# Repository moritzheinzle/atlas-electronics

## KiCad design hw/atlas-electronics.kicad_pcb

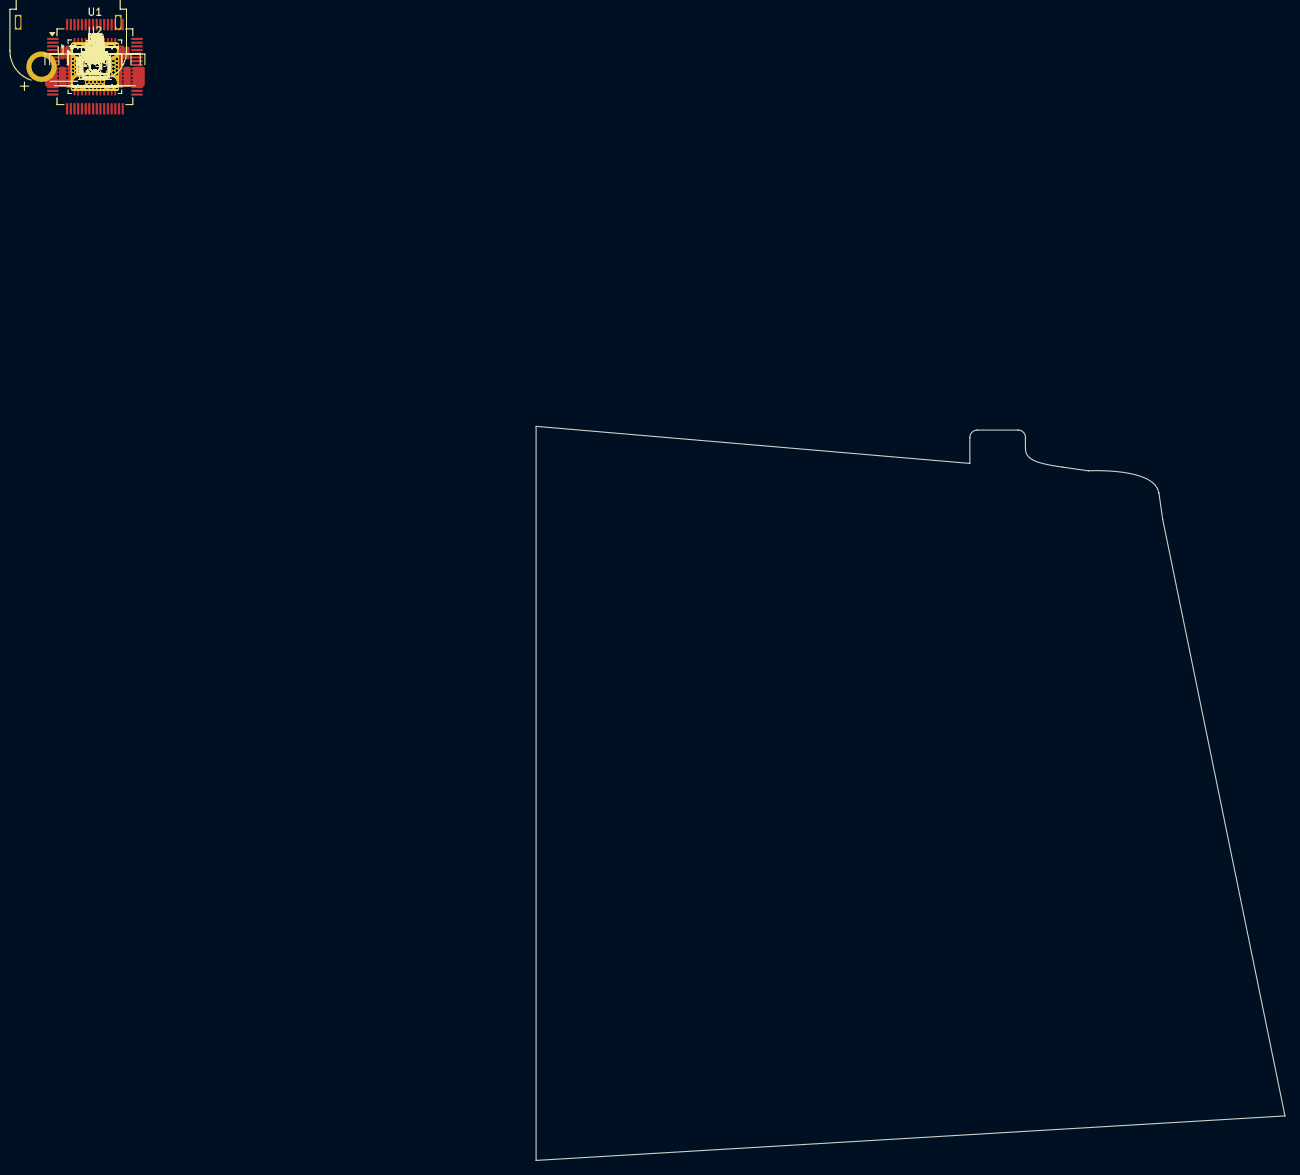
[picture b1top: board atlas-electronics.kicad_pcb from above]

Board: 2 copper layers, 101.0 x 99.0 mm, 185 parts (0 on the bottom side), 95 nets, no tracks yet.

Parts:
C1, C3, C4, C5, C6, C8, C11, C14, C17, C18, C24, C27, C30, C37, C38, C40, C41, C42, C43, C44, C45: 100n X7R 50V; C_0603_1608Metric
C2, C10, C39: 4u7 X5R 16V; C_0603_1608Metric
C7, C9, C12, C16: 1u X5R 50V; C_0603_1608Metric
C13, C19, C25, C26, C28, C29, C31, C32: 4u7 X7R 50V; C_1206_3216Metric
C15: 47n X7R 50V; C_0603_1608Metric
C20: 10u X5R 25V; C_0805_2012Metric
C21, C22, C23, C33, C34, C35: 3n3 X7R 100V; C_0603_1608Metric
C36: 10n X7R 50V; C_0603_1608Metric
C46, C47, C48, C49, C50, C51, C52, C53, C55, C56, C57, C58, C59, C60: C_Small; C_0603_1608Metric
C54, C61: 100n; WDFN-10-1EP_3x3mm_P0.5mm_EP1.8x2.5mm
C62: C_Small; WDFN-10-1EP_3x3mm_P0.5mm_EP1.8x2.5mm
C63, C64: 10pF; C_0603_1608Metric
C65, C66, C67, C68: 1u X7R 25V; C_0603_1608Metric
D1: SS16; D_SOD-123
D2, D3, D4: 1A 40V; D_SOD-123
D5, D6#2, D7#2, D8#2, D9: SK6805; LED_SK6812_EC15_1.5x1.5mm
D6, D7, D8, D9#2: SK6805; LED_SK6805_PLCC4_2.4x2.7mm_P1.3mm
D10: PESD2CANFD24V-TR; SOT-23
D11, D12: BAT48ZFILM; D_SOD-123
D13: SD05C-01F; D_SOD-323
D14, D15: GREEN; LED_0805_2012Metric
FB1: 120@100MHz; L_0603_1608Metric
J1, J2, J3: Conn_01x01; Goated holy pad
J4, J6, J10: Conn_01x03_MountingPin; JST_GH_SM03B-GHS-TB_1x03-1MP_P1.25mm_Horizontal
J5: Conn_01x08_MountingPin; JST_GH_SM08B-GHS-TB_1x08-1MP_P1.25mm_Horizontal
J7: Conn_01x05_MountingPin; JST_GH_SM05B-GHS-TB_1x05-1MP_P1.25mm_Horizontal
J8: Conn_01x07_MountingPin; JST_GH_SM07B-GHS-TB_1x07-1MP_P1.25mm_Horizontal
J9: Conn_01x06_MountingPin; AMASS_XT60PW-F_1x02_P7.20mm_Horizontal
J11: SM02B-SRSS-TB; JST_SH_SM02B-SRSS-TB_1x02-1MP_P1.00mm_Horizontal
JP1, JP2, JP3, JP4, JP5: SolderJumper_2_Open; WSON-8-1EP_6x5mm_P1.27mm_EP3.4x4mm
L1: 33uH; L_APV_ANR6020
Q1, Q2, Q3, Q4, Q5, Q6: ISC025N06LM6; TDSON-8-1
R1, R15, R16, R17: 10k 1%; R_0603_1608Metric
R2, R14: 100k 1%; R_0603_1608Metric
R11, R12, R13: 2m 3W 1%; R_2512_6332Metric
R18, R19, R20, R22, R23, R27, R28, R29, R30: 100R; R_0201_0603Metric
R21, R24: 60R4; R_0603_1608Metric
R25: 2k; R_0201_0603Metric
R26: 1k; R_0201_0603Metric
R31: 10k; R_0201_0603Metric
R36: 330; R_0402_1005Metric
R37: 1k; R_0402_1005Metric
TH1: Thermistor_NTC; R_0603_1608Metric
TP1, TP2, TP3, TP4, TP5, TP6, TP7, TP8, TP9, TP10, TP11, TP12, TP13, TP14, TP24, TP25, TP26, TP27, TP28, TP29, TP30, TP31, TP32, TP33, TP34, TP35, TP36, TP37, TP38, TP41: TestPoint_Small; TestPoint_Pad_D1.0mm
TP15, TP16, TP17, TP18, TP19, TP20, TP21, TP22, TP23: TestPoint; TestPoint_Pad_D1.0mm
TP39: TestPoint_Small; TestPoint-D0.4
U1: STM32G473RCTx; LQFP-64_10x10mm_P0.5mm
U2: Texas_RGZ0048A_VQFN-48-1EP_7x7mm_P0.5mm_EP5.15x5.15mm_Therm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
U3: AS5047D; TSSOP-14_4.4x5mm_P0.65mm
U4: SN74LV1T125DCK; SOT-353_SC-70-5
U5: TCAN334G; TSSOP-14_4.4x5mm_P0.65mm
U6: AP2112K-3.3; SOT-23-5
U7: TPS7A20xxxDBV; SOT-23-5
Y1: Crystal_GND24; Crystal_SMD_3225-4Pin_3.2x2.5mm

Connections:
+3V3: C1.1, C2.1, C3.1, C4.1, C5.1, C6.1, C39.1, C47.1, C54.1, C56.1, C61.1, C62.1, C65.1, J5.2, J7.1, J8.2, J9.1, J10.1, R1.1, R16.1, R17.1, R31.2, R36.1, TP41.1 (1_1), U1.1 (VBAT), U1.16 (VDD), U1.32 (VDD), U1.48 (VDD), U1.64 (VDD), U3.11 (VDD), U3.12 (VDD3V3), U5.3 (VCC), U6.5 (VOUT)
+3V3A: C9.1, C17.1, C68.1, FB1.1, U2.26 (VREF), U7.5 (OUT)
+5V: C20.1, C40.1, C41.1, C42.1, C43.1, C44.1, C45.1, C46.1, C55.1, C66.1, C67.1, D5.4 (VDD), D6.4 (VDD), D6#2.4 (VDD), D7.4 (VDD), D7#2.4 (VDD), D8.4 (VDD), D8#2.4 (VDD), D9.4 (VDD), D9#2.4 (VDD), J5.1, J8.1, L1.2, R37.1, TP39.1 (1_1), U4.5 (VCC), U6.1 (VIN), U6.3 (EN), U7.1 (IN), U7.3 (EN)
+VBAT: C12.1, C13.1, C14.1, C19.1, C24.1, C25.1, C26.1, C27.1, C28.1, C29.1, C30.1, C31.1, C32.1, Q1.5 (D), Q2.5 (D), Q3.5 (D), R2.1, R14.1, U2.6 (VM), U2.7 (VDRAIN), U2.47 (VIN)
/FOC - Gate Driver/CUR_SENSE_A: TP5.1 (1_1), U1.12 (PA0), U2.25 (SOA)
/FOC - Gate Driver/CUR_SENSE_B: TP6.1 (1_1), U1.21 (PA7), U2.24 (SOB)
/FOC - Gate Driver/CUR_SENSE_C: TP7.1 (1_1), U1.25 (PB1), U2.23 (SOC)
/FOC - Gate Driver/GHA: Q1.4 (G), TP15.1 (1_1), U2.8 (GHA)
/FOC - Gate Driver/GHB: Q2.4 (G), TP18.1 (1_1), U2.17 (GHB)
/FOC - Gate Driver/GHC: Q3.4 (G), TP21.1 (1_1), TP23.1 (1_1), U2.18 (GHC)
/FOC - Gate Driver/GLA: D2.1 (K), Q4.4 (G), TP17.1 (1_1), U2.10 (GLA)
/FOC - Gate Driver/GLB: D3.1 (K), Q5.4 (G), TP20.1 (1_1), U2.15 (GLB)
/FOC - Gate Driver/GLC: D4.1 (K), Q6.4 (G), U2.20 (GLC)
/FOC - Gate Driver/PWM_A: TP8.1 (1_1), U1.8 (PC0), U2.37 (INHA)
/FOC - Gate Driver/PWM_A_N: TP11.1 (1_1), U1.35 (PB13), U2.38 (INLA)
/FOC - Gate Driver/PWM_B: TP9.1 (1_1), U1.9 (PC1), U2.39 (INHB)
/FOC - Gate Driver/PWM_B_N: TP12.1 (1_1), U1.36 (PB14), U2.40 (INLB)
/FOC - Gate Driver/PWM_C: TP10.1 (1_1), U1.10 (PC2), U2.41 (INHC)
/FOC - Gate Driver/PWM_C_N: TP13.1 (1_1), U1.37 (PB15), U2.42 (INLC)
/FOC - Gate Driver/SHA: C21.2, C33.1, J1.1 (Pin_1_1), Q1.1 (S), Q1.2 (S), Q1.3 (S), Q4.5 (D), TP16.1 (1_1), U2.9 (SHA)
/FOC - Gate Driver/SHB: C22.2, C34.1, J2.1 (Pin_1_1), Q2.1 (S), Q2.2 (S), Q2.3 (S), Q5.5 (D), TP19.1 (1_1), U2.16 (SHB)
/FOC - Gate Driver/SHC: C23.2, C35.1, J3.1 (Pin_1_1), Q3.1 (S), Q3.2 (S), Q3.3 (S), Q6.5 (D), TP22.1 (1_1), U2.19 (SHC)
/FOC - Gate Driver/SPA: C24.2, C25.2, C26.2, Q4.1 (S), Q4.2 (S), Q4.3 (S), R11.1, U2.11 (SPA)
/FOC - Gate Driver/SPB: C27.2, C28.2, C29.2, Q5.1 (S), Q5.2 (S), Q5.3 (S), R12.1, U2.14 (SPB)
/FOC - Gate Driver/SPC: C30.2, C31.2, C32.2, Q6.1 (S), Q6.2 (S), Q6.3 (S), R13.1, U2.21 (SPC)
/FOC - Gate Driver/SPI_DRV_CS: TP4.1 (1_1), U1.51 (PA15), U2.32 (~SCS)
/FOC - Gate Driver/SPI_DRV_MISO: TP2.1 (1_1), U1.53 (PC11), U2.29 (SDO)
/FOC - Gate Driver/SPI_DRV_MOSI: TP3.1 (1_1), U1.54 (PC12), U2.30 (SDI)
/FOC - Gate Driver/SPI_DRV_SCK: TP1.1 (1_1), U1.52 (PC10), U2.31 (SCLK)
/FOC - Inverter/SNUBH_A: C21.1, C22.1, C23.1
/FOC - Inverter/SNUBL_A: C33.2, C34.2, C35.2
/Interface - FDCAN Tran./FDCAN_H: D10.2 (K), J4.2, J6.2, JP1.1 (A), U5.7 (CANH)
/Interface - FDCAN Tran./FDCAN_L: D10.1 (K), J4.1, J6.1, JP2.1 (A), U5.6 (CANL)
/Interface - FDCAN Tran./FDCAN_RX: TP25.1 (1_1), U1.45 (PA11), U5.4 (RXD)
/Interface - FDCAN Tran./FDCAN_TX: TP26.1 (1_1), U1.46 (PA12), U5.1 (TXD)
/Interface - Interconnects/AUX1: C52.1, R18.2, U1.14 (PA2)
/Interface - Interconnects/AUX2: C51.1, R19.2, U1.17 (PA3)
/Interface - Interconnects/AUX3: C50.1, R20.2, U1.20 (PA6)
/Interface - Interconnects/AUX4: C49.1, R22.2, U1.22 (PC4)
/Interface - Interconnects/AUX5: C48.1, R23.2, U1.23 (PC5)
/Interface - Interconnects/AUX6: C60.1, R26.1, R27.2, U1.60 (PB7)
/Interface - Interconnects/AUX7: C59.1, R28.2, U1.61 (PB8)
/Interface - Interconnects/AUX8: C58.1, R29.2, U1.62 (PB9)
/Interface - Interconnects/AUX9: C57.1, R25.1, R30.2, U1.38 (PC6)
/Interface - Interconnects/I2C4_PULLUP: D11.2 (A), D12.2 (A), U1.19 (PA5)
/Interface - Interconnects/NRST: J7.4, U1.7 (PG10)
/Interface - Interconnects/NTC_MOTOR: C38.1, J11.1, R17.2, TP27.1 (1_1), U1.43 (PA9)
/Interface - Interconnects/SPI_ENC_MISO: TP30.1 (1_1), U1.57 (PB4), U3.3 (MISO)
/Interface - Interconnects/SPI_ENC_MOSI: TP31.1 (1_1), U1.58 (PB5), U3.4 (MOSI)
/Interface - Interconnects/SPI_ENC_SCK: J9.2, TP29.1 (1_1), U1.56 (PB3), U3.2 (CLK)
/Interface - Interconnects/SWCLK: J7.3, U1.50 (PA14)
/Interface - Interconnects/SWDIO: J7.2, U1.49 (PA13)
/MCU - IO Domain/ADC_VBUS: C36.1, R14.2, R15.1, U1.34 (PB12)
/MCU - IO Domain/DRV_EN: TP14.1 (1_1), U1.33 (PB11), U2.33 (ENABLE)
/MCU - IO Domain/DRV_nF: R1.2, TP24.1 (1_1), U1.39 (PC7), U2.28 (~FAULT)
/MCU - IO Domain/EXT_HOMING_INT: D13.2 (A2), J10.2, TP34.1 (1_1), U1.2 (PC13)
/MCU - IO Domain/NTC_INVERTER: C37.1, R16.2, TH1.1, TP28.1 (1_1), U1.42 (PA8)
/MCU - IO Domain/OSC_OUT: C64.1, U1.6 (PF1), Y1.3
/MCU - IO Domain/SPI_ENC_CS_EXT: R31.1, TP35.1 (1_1), U1.59 (PB6)
/MCU - IO Domain/SPI_ENC_CS_ONB: TP32.1 (1_1), U1.55 (PD2), U3.1 (~CS)
/MCU - IO Domain/STATUS_LED: TP33.1 (1_1), U1.13 (PA1), U4.2 (A)
/MCU - IO Domain/UID_A: JP3.2 (B), TP36.1 (1_1), U1.40 (PC8)
/MCU - IO Domain/UID_B: JP4.2 (B), TP37.1 (1_1), U1.41 (PC9)
/MCU - IO Domain/UID_C: JP5.2 (B), TP38.1 (1_1), U1.44 (PA10)
GND: C1.2, C2.2, C3.2, C4.2, C5.2, C6.2, C7.2, C8.2, C9.2, C10.2, C11.2, C13.2, C14.2, C16.2, C17.2, C19.2, C20.2, C36.2, C37.2, C38.2, C39.2, C40.2, C41.2, C42.2, C43.2, C44.2, C45.2, C46.2, C47.2, C48.2, C49.2, C50.2, C51.2, C52.2, C53.2, C54.2, C55.2, C56.2, C57.2, C58.2, C59.2, C60.2, C61.2, C62.2, C63.2, C64.2, C65.2, C66.2, C67.2, C68.2, D1.2 (A), D2.2 (A), D3.2 (A), D4.2 (A), D5.2 (VSS), D6.2 (VSS), D6#2.2 (VSS), D7.2 (VSS), D7#2.2 (VSS), D8.2 (VSS), D8#2.2 (VSS), D9.2 (VSS), D9#2.2 (VSS), D10.3 (A), D13.1 (A1), D14.1 (K), D15.1 (K), J4.3, J4.MP (MountPin), J5.8, J5.MP (MountPin), J6.3, J6.MP (MountPin), J7.5, J7.MP (MountPin), J8.7, J8.MP (MountPin), J10.3, J10.MP (MountPin), J11.2, JP3.1 (A), JP4.1 (A), JP5.1 (A), R11.2, R12.2, R13.2, R15.2, TH1.2, U1.15 (VSS), U1.27 (VSSA), U1.31 (VSS), U1.47 (VSS), U1.63 (VSS), U2.2 (PGND), U2.12 (SNA), U2.13 (SNB), U2.22 (SNC), U2.27 (DGND), U2.35 (AGND), U2.43 (BGND), U2.49 (PAD), U3.13 (GND), U4.1 (~OE), U4.3 (GND), U5.2 (GND), U6.2 (GND), U7.2 (GND), Y1.2 (G), Y1.4 (G)
unnamed: C53.1, R21.2, R24.1
unnamed: C63.1, Y1.1
unnamed: C18.2, D1.1 (K), L1.1, U2.45 (SW)
unnamed: D5.3 (DIN), U4.4 (Y)
unnamed: D5.1 (DOUT), D6.3 (DIN), D6#2.3 (DIN)
unnamed: D6.1 (DOUT), D6#2.1 (DOUT), D7.3 (DIN), D7#2.3 (DIN)
unnamed: D7.1 (DOUT), D7#2.1 (DOUT), D8.3 (DIN), D8#2.3 (DIN)
unnamed: D8.1 (DOUT), D8#2.1 (DOUT), D9.3 (DIN), D9#2.3 (DIN)
unnamed: D11.1 (K), R25.2
unnamed: D12.1 (K), R26.2
unnamed: D14.2 (A), R37.2
unnamed: D15.2 (A), R36.2
unnamed: J5.3, R18.1
unnamed: J5.4, R19.1
unnamed: J5.5, R20.1
unnamed: J5.6, R22.1
unnamed: J5.7, R23.1
unnamed: J8.3, R27.1
unnamed: J8.4, R28.1
unnamed: J8.5, R29.1
unnamed: J8.6, R30.1
unnamed: JP1.2 (B), R21.1
unnamed: JP2.2 (B), R24.2
unnamed: C7.1, C8.1, C10.1, C11.1, FB1.2, U1.28 (VREF+), U1.29 (VDDA)
unnamed: C15.1, U2.4 (CPH)
unnamed: C15.2, U2.3 (CPL)
unnamed: C16.1, U2.36 (DVDD)
unnamed: C12.2, U2.5 (VCP)
unnamed: C18.1, U2.44 (CB)
unnamed: R2.2, U2.48 (~SHDN)
